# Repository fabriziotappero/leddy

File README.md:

This is the repository of LEDDY, a 60W modular LED panel build using the very
 efficient and clean 1W LED YJ-BC-3030-G01 from yuji.com.

LEDDY is an open-source LED pannel designed to be a valid light source for the 
film industry.

For more information contact the developer at:

[www.focusaway.com](https://www.focusaway.com)

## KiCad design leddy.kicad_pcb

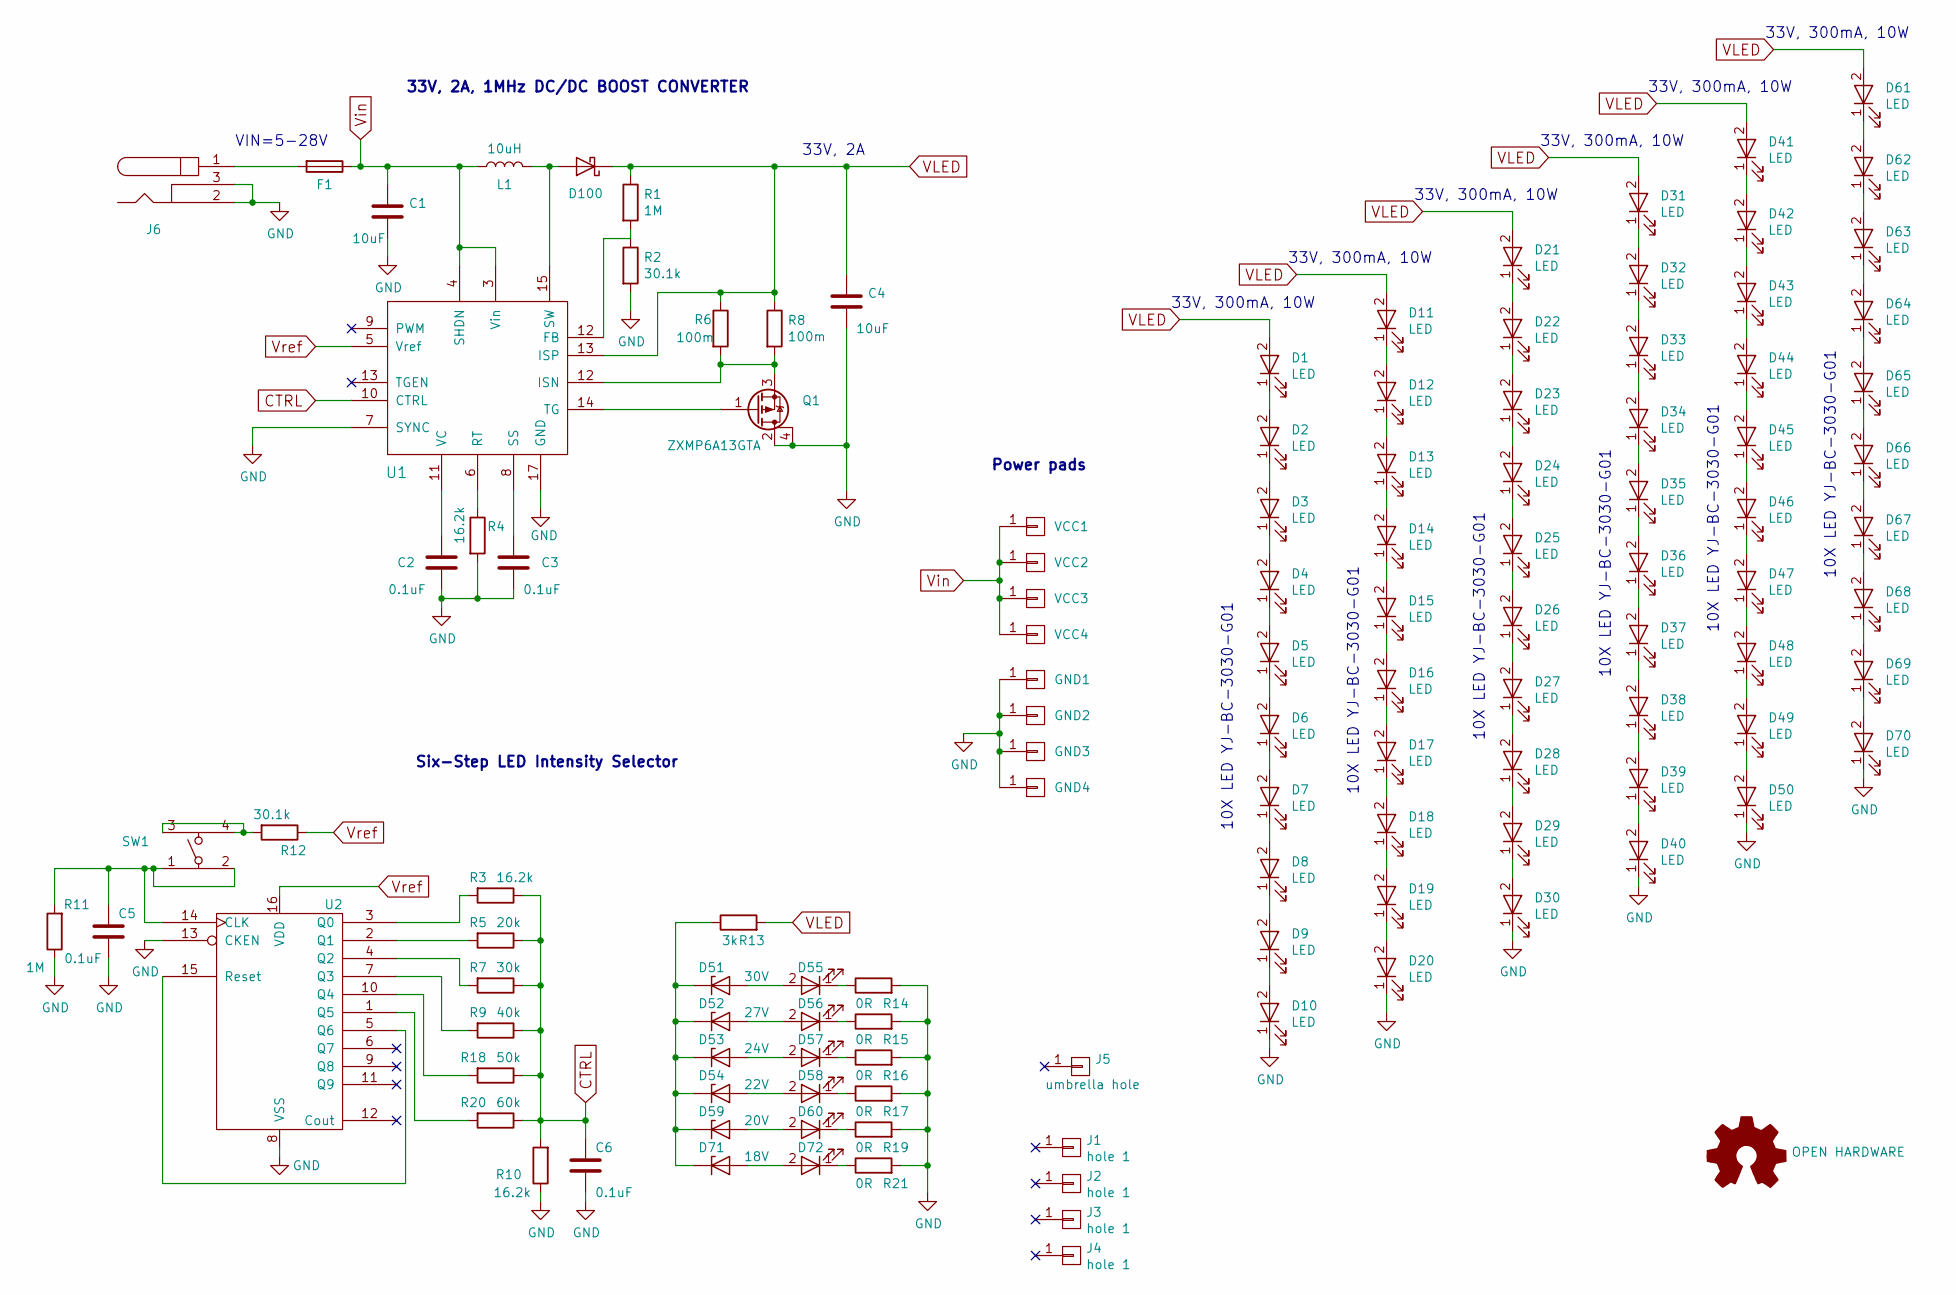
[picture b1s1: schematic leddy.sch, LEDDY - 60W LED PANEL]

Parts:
C1, C4: 10uF; L_Vishay_IHLP-2020
C2, C3, C5, C6: 0.1uF; C_0603_HandSoldering
D1, D2, D3, D4, D5, D6, D7, D8, D9, D10, D11, D12, D13, D14, D15, D16, D17, D18, D19, D20, D21, D22, D23, D24, D25, D26, D27, D28, D29, D30, D31, D32, D33, D34, D35, D36, D37, D38, D39, D40, D41, D42, D43, D44, D45, D46, D47, D48, D49, D50, D61, D62, D63, D64, D65, D66, D67, D68, D69, D70: LED; LED-3030
D51: 30V; D_0603
D52: 27V; D_0603
D53: 24V; D_0603
D54: 22V; D_0603
D55, D56, D57, D58, D60, D72: LED; LED_PLCC-2
D59: 20V; D_0603
D71: 18V; D_0603
D100: SS3P4LHM3_A/H; TO-277A
F1: Fuse; Fuse_SMD1206_Reflow
GND1, GND2, GND3, GND4: none; Test_Point_Keystone_5019_Minature
J1, J2, J3, J4: hole 1; MountingHole_3.2mm_M3_ISO7380_Pad
J5: umbrella hole; MountingHole_8.4mm_M8
J6: PJ-002AH-SMT-TR
J7: OPEN HARDWARE; OSHW-Logo_5.7x6mm_SilkScreen
L1: 10uH; L_Vishay_IHLP-2525
Q1: ZXMP6A13GTA; SOT-223
R1, R11: 1M; R_0603_HandSoldering
R2, R12: 30.1k; R_0603_HandSoldering
R3, R4, R10: 16.2k; R_0603_HandSoldering
R5: 20k; R_0603_HandSoldering
R6, R8: 100m; R_1206_HandSoldering
R7: 30k; R_0603_HandSoldering
R9: 40k; R_0603_HandSoldering
R13: 3k; R_0603_HandSoldering
R14, R15, R16, R17, R19, R21: 0R; R_0603_HandSoldering
R18: 50k; R_0603_HandSoldering
R20: 60k; R_0603_HandSoldering
SW1: PTS645SM70SMTR92; sw_push4p
U1: LT3518EFE#PBF; TSSOP-16-1EP_4.4x5mm_Pitch0.65mm-thermal
U2: 74HC4017PW; TSSOP-16_4.4x5mm_Pitch0.65mm
VCC1, VCC2, VCC3, VCC4: none; Test_Point_Keystone_5019_Minature

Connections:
CTRL: C6.1, R3.1, R5.1, R7.1, R9.1, R10.2, R18.1, R20.1, U1.10 (CTRL)
GND: C1.2, C2.2, C3.2, C4.2, C5.2, C6.2, D10.1 (K), D20.1 (K), D30.1 (K), D40.1 (K), D50.1 (K), D70.1 (K), GND1.1, GND2.1, GND3.1, GND4.1, J6.2, J6.3, Q1.2 (D), Q1.4 (D), R2.2, R4.2, R10.1, R11.1, R14.2, R15.2, R16.2, R17.2, R19.2, R21.2, U1.7 (SYNC), U1.17 (GND), U2.8 (VSS), U2.13 (CKEN)
unnamed: C2.1, U1.11 (VC)
unnamed: C3.1, U1.8 (SS)
unnamed: C5.1, R11.2, SW1.1, SW1.2, U2.14 (CLK)
unnamed: D1.1 (K), D2.2 (A)
unnamed: D2.1 (K), D3.2 (A)
unnamed: D3.1 (K), D4.2 (A)
unnamed: D4.1 (K), D5.2 (A)
unnamed: D5.1 (K), D6.2 (A)
unnamed: D6.1 (K), D7.2 (A)
unnamed: D7.1 (K), D8.2 (A)
unnamed: D8.1 (K), D9.2 (A)
unnamed: D9.1 (K), D10.2 (A)
unnamed: D11.1 (K), D12.2 (A)
unnamed: D12.1 (K), D13.2 (A)
unnamed: D13.1 (K), D14.2 (A)
unnamed: D14.1 (K), D15.2 (A)
unnamed: D15.1 (K), D16.2 (A)
unnamed: D16.1 (K), D17.2 (A)
unnamed: D17.1 (K), D18.2 (A)
unnamed: D18.1 (K), D19.2 (A)
unnamed: D19.1 (K), D20.2 (A)
unnamed: D21.1 (K), D22.2 (A)
unnamed: D22.1 (K), D23.2 (A)
unnamed: D23.1 (K), D24.2 (A)
unnamed: D24.1 (K), D25.2 (A)
unnamed: D25.1 (K), D26.2 (A)
unnamed: D26.1 (K), D27.2 (A)
unnamed: D27.1 (K), D28.2 (A)
unnamed: D28.1 (K), D29.2 (A)
unnamed: D29.1 (K), D30.2 (A)
unnamed: D31.1 (K), D32.2 (A)
unnamed: D32.1 (K), D33.2 (A)
unnamed: D33.1 (K), D34.2 (A)
unnamed: D34.1 (K), D35.2 (A)
unnamed: D35.1 (K), D36.2 (A)
unnamed: D36.1 (K), D37.2 (A)
unnamed: D37.1 (K), D38.2 (A)
unnamed: D38.1 (K), D39.2 (A)
unnamed: D39.1 (K), D40.2 (A)
unnamed: D41.1 (K), D42.2 (A)
unnamed: D42.1 (K), D43.2 (A)
unnamed: D43.1 (K), D44.2 (A)
unnamed: D44.1 (K), D45.2 (A)
unnamed: D45.1 (K), D46.2 (A)
unnamed: D46.1 (K), D47.2 (A)
unnamed: D47.1 (K), D48.2 (A)
unnamed: D48.1 (K), D49.2 (A)
unnamed: D49.1 (K), D50.2 (A)
unnamed: D51.1 (K), D52.1 (K), D53.1 (K), D54.1 (K), D59.1 (K), D71.1 (K), R13.1
unnamed: D51.2 (A), D55.2 (A)
unnamed: D52.2 (A), D56.2 (A)
unnamed: D53.2 (A), D57.2 (A)
unnamed: D54.2 (A), D58.2 (A)
unnamed: D55.1 (K), R14.1
unnamed: D56.1 (K), R15.1
unnamed: D57.1 (K), R16.1
unnamed: D58.1 (K), R17.1
unnamed: D59.2 (A), D60.2 (A)
unnamed: D60.1 (K), R19.1
unnamed: D61.1 (K), D62.2 (A)
unnamed: D62.1 (K), D63.2 (A)
unnamed: D63.1 (K), D64.2 (A)
unnamed: D64.1 (K), D65.2 (A)
unnamed: D65.1 (K), D66.2 (A)
unnamed: D66.1 (K), D67.2 (A)
unnamed: D67.1 (K), D68.2 (A)
unnamed: D68.1 (K), D69.2 (A)
unnamed: D69.1 (K), D70.2 (A)
unnamed: D71.2 (A), D72.2 (A)
unnamed: D72.1 (K), R21.1
unnamed: D100.2 (A), L1.2, U1.15 (SW)
unnamed: F1.2, J6.1
unnamed: Q1.1 (G), U1.14 (TG)
unnamed: R3.2, U2.3 (Q0)
unnamed: R4.1, U1.6 (RT)
unnamed: R5.2, U2.2 (Q1)
unnamed: R7.2, U2.4 (Q2)
unnamed: R9.2, U2.7 (Q3)
unnamed: R12.2, SW1.3, SW1.4
unnamed: R18.2, U2.10 (Q4)
unnamed: R20.2, U2.1 (Q5)
unnamed: U2.5 (Q6), U2.15 (Reset)
VLED: C4.1, D1.2 (A), D11.2 (A), D21.2 (A), D31.2 (A), D41.2 (A), D61.2 (A), D100.1 (K), R1.1, R6.1, R8.1, R13.2, U1.13 (ISP)
Vin: C1.1, F1.1, L1.1, U1.3 (Vin), U1.4 (SHDN), VCC1.1, VCC2.1, VCC3.1, VCC4.1
Vref: R12.1, U1.5 (Vref), U2.16 (VDD)

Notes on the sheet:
33V, 300mA, 10W
10X LED YJ-BC-3030-G01
33V, 2A
VIN=5-28V
33V, 2A, 1MHz DC/DC BOOST CONVERTER
Six-Step LED Intensity Selector
Power pads

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
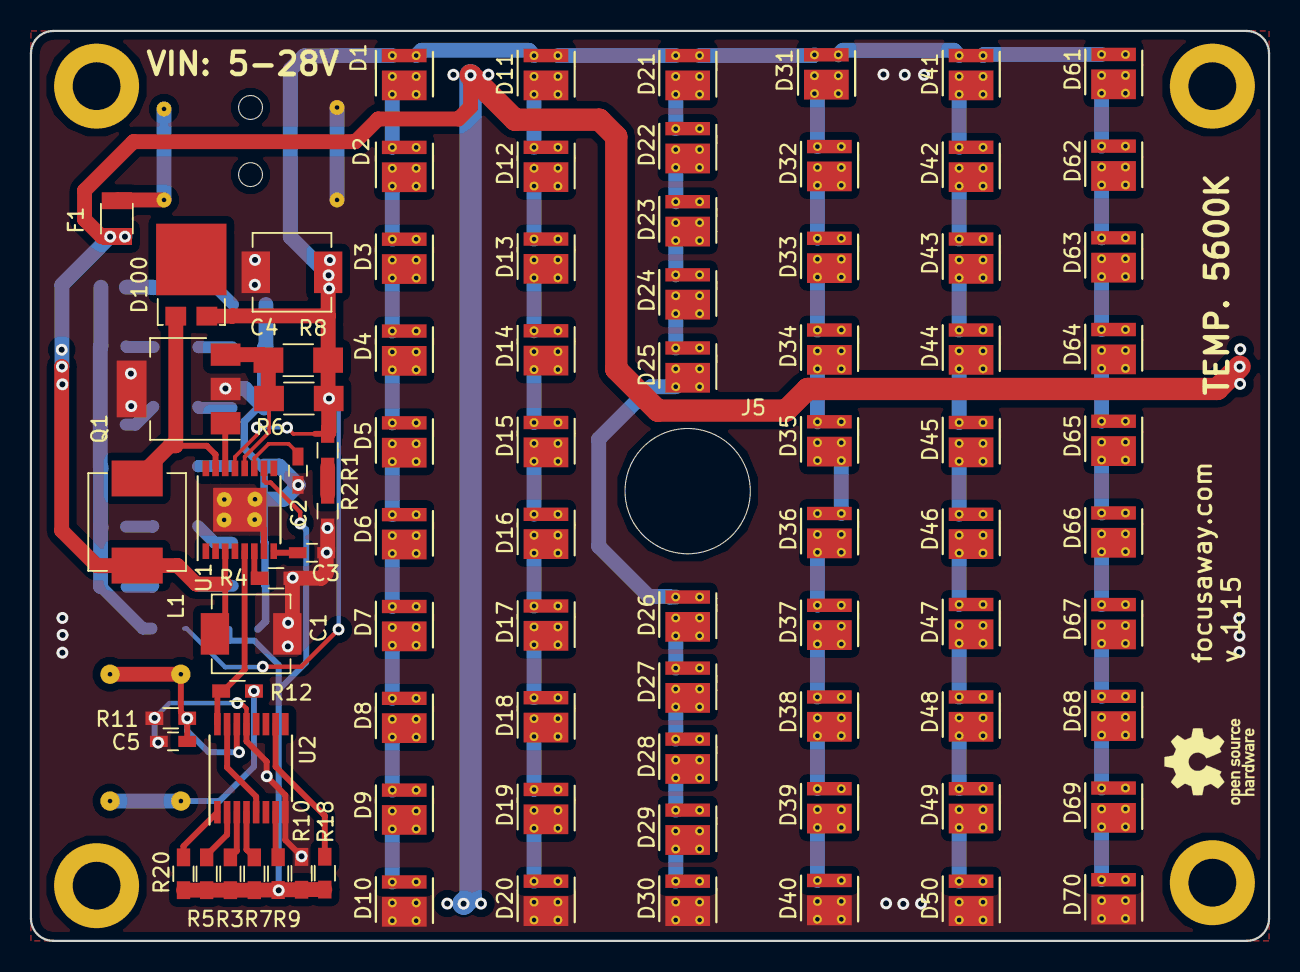
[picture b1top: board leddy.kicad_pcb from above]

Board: 2 copper layers, 83.0 x 61.0 mm, 121 parts (0 on the bottom side), 89 nets.

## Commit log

2017-04-19 LED panel PCB started
2017-04-25 added LED driver IC and added a total of 50 LEDs
2017-04-25 added readme file
2017-05-03 layout almost done
2017-05-03 minor
2017-05-04 added the LED intensity selection circuit
2017-05-04 added simple debouncing circuit (to be tested)
2017-05-05 started PCB layouting
2017-05-05 added led current level indication
2017-05-08 added schematic pdf and fixed template info
2017-05-08 added better LED current level meter
2017-07-24 total power is now 60W and there are 6 level of led power regulation
2017-07-25 pcb rounted

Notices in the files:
leddy.kicad_pcb:
Copyright Fabrizio Tappero
leddy.sch:
Copyright 2017 Fabrizo Tappero
